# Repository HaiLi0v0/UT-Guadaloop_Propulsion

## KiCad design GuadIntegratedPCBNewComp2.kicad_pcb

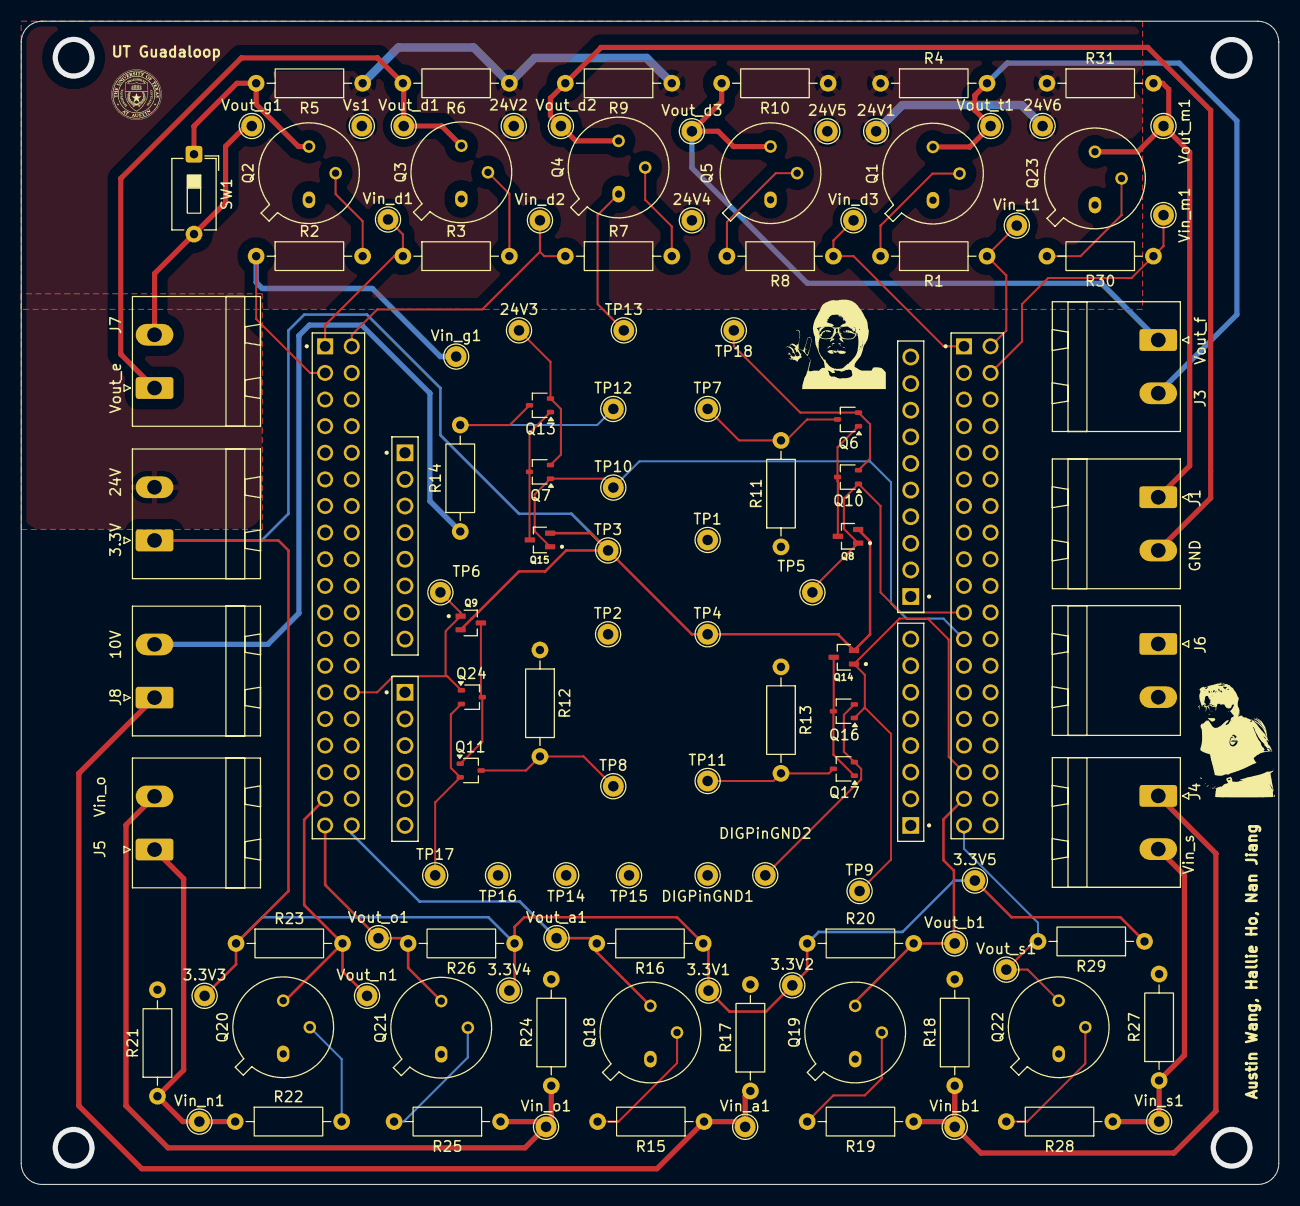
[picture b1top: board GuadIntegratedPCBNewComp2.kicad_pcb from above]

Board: 2 copper layers, 120.0 x 111.0 mm, 118 parts (0 on the bottom side), 50 nets.

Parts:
3.3V1, 3.3V2, 3.3V3, 3.3V4, 3.3V5, 24V1, 24V2, 24V4, 24V5, 24V6: Vs; TestPoint_THTPad_D2.0mm_Drill1.0mm
24V3: Vs GND; TestPoint_THTPad_D2.0mm_Drill1.0mm
DIGPinGND1, DIGPinGND2: V4 GND; TestPoint_THTPad_D2.0mm_Drill1.0mm
J1, J2, J3, J4, J5, J6, J7, J8: Screw_Terminal_01x02; PhoenixContact_MSTBA_2,5_2-G-5,08_1x02_P5.08mm_Horizontal
Q1, Q2, Q3, Q4, Q5, Q18, Q19, Q20, Q21, Q22, Q23: 2N2219; TO-39-3
Q6, Q7, Q10, Q11, Q13, Q16, Q17, Q24: BSS214NW; SOT-323_SC-70
Q8, Q9, Q14, Q15: BSS209PW_H6327; SOT65P210X100-3N
R1, R2, R3, R7, R8, R15, R19, R22, R25, R28, R30: 25k; R_Axial_DIN0207_L6.3mm_D2.5mm_P10.16mm_Horizontal
R4, R5, R6, R9, R10, R11, R12, R13, R14, R16, R20, R23, R26, R29, R31: 1200; R_Axial_DIN0207_L6.3mm_D2.5mm_P10.16mm_Horizontal
R17, R18, R21, R24, R27: 100k; R_Axial_DIN0207_L6.3mm_D2.5mm_P10.16mm_Horizontal
SW1: SW_SPST; SW_DIP_SPSTx01_Slide_6.7x4.1mm_W7.62mm_P2.54mm_LowProfile
TP1, TP2: V2 = 10 V; TestPoint_THTPad_D2.0mm_Drill1.0mm
TP3, TP4: V1 = 3.3; TestPoint_THTPad_D2.0mm_Drill1.0mm
TP5, TP6: V4 = 3.3 Pulse; TestPoint_THTPad_D2.0mm_Drill1.0mm
TP7, TP8, TP11, TP12: Vo; TestPoint_THTPad_D2.0mm_Drill1.0mm
TP9, TP10: V3 = 3.3 PULSE; TestPoint_THTPad_D2.0mm_Drill1.0mm
TP13, TP16: V1 GND; TestPoint_THTPad_D2.0mm_Drill1.0mm
TP14, TP17: V3 GND; TestPoint_THTPad_D2.0mm_Drill1.0mm
TP15, TP18: V2 GND; TestPoint_THTPad_D2.0mm_Drill1.0mm
U1: NUCLEO-F446RE; MODULE_NUCLEO-F446RE
Vin_a1: 24V; TestPoint_THTPad_D2.0mm_Drill1.0mm
Vin_b1: 5V; TestPoint_THTPad_D2.0mm_Drill1.0mm
Vin_d1, Vin_d2, Vin_d3: 5V; TestPoint_THTPad_D2.0mm_Drill1.0mm
Vin_g1: Vs; TestPoint_THTPad_D2.0mm_Drill1.0mm
Vin_m1: 5V; TestPoint_THTPad_D2.0mm_Drill1.0mm
Vin_n1: 5V; TestPoint_THTPad_D2.0mm_Drill1.0mm
Vin_o1: 5V; TestPoint_THTPad_D2.0mm_Drill1.0mm
Vin_s1: 5V; TestPoint_THTPad_D2.0mm_Drill1.0mm
Vin_t1: Vs; TestPoint_THTPad_D2.0mm_Drill1.0mm
Vout_a1: Vs; TestPoint_THTPad_D2.0mm_Drill1.0mm
Vout_b1: Vs; TestPoint_THTPad_D2.0mm_Drill1.0mm
Vout_d1, Vout_d2, Vout_d3: Vs; TestPoint_THTPad_D2.0mm_Drill1.0mm
Vout_g1: Vs; TestPoint_THTPad_D2.0mm_Drill1.0mm
Vout_m1: Vs; TestPoint_THTPad_D2.0mm_Drill1.0mm
Vout_n1: Vs; TestPoint_THTPad_D2.0mm_Drill1.0mm
Vout_o1: Vs; TestPoint_THTPad_D2.0mm_Drill1.0mm
Vout_s1: Vs; TestPoint_THTPad_D2.0mm_Drill1.0mm
Vout_t1: Vs; TestPoint_THTPad_D2.0mm_Drill1.0mm
Vs1: Vs; TestPoint_THTPad_D2.0mm_Drill1.0mm

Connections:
3.3V: 3.3V1.1, 3.3V2.1, 3.3V3.1, 3.3V4.1, 3.3V5.1, J2.1, Q8.2 (S), Q9.2 (S), Q14.2 (S), Q15.2 (S), R16.1, R20.1, R23.1, R26.1, R29.1, TP3.1, TP4.1
3v3Pulse1: Q9.1 (G), Q24.1 (G), TP6.1, U1.CN7_28 (PA0)
3v3Pulse2: Q7.1 (G), Q15.1 (G), TP10.1, U1.CN10_23 (PA8)
3v3Pulse3: Q8.1 (G), Q10.1 (G), TP5.1, U1.CN10_21 (PA9)
3v3Pulse4: Q14.1 (G), Q16.1 (G), TP9.1, U1.CN10_33 (PA10)
10v: J8.2, R11.1, R12.1, R13.1, R14.1, TP1.1, TP2.1
24v: 24V1.1, 24V2.1, 24V4.1, 24V5.1, 24V6.1, J2.2, R4.1, R5.1, R6.1, R9.1, R10.1, R31.1, Vs1.1
GND: 24V3.1, DIGPinGND1.1, DIGPinGND2.1, J6.1, J6.2, Q1.1 (E), Q2.1 (E), Q3.1 (E), Q4.1 (E), Q5.1 (E), Q6.2 (S), Q7.2 (S), Q10.2 (S), Q11.2 (S), Q13.2 (S), Q16.2 (S), Q17.2 (S), Q18.1 (E), Q19.1 (E), Q20.1 (E), Q21.1 (E), Q22.1 (E), Q23.1 (E), Q24.2 (S), R17.2, R18.2, R21.2, R24.2, R27.2, TP13.1, TP14.1, TP15.1, TP16.1, TP17.1, TP18.1, U1.CN6_6 (CN6_GND), U1.CN6_7 (CN6_GND__1)
unnamed: Q1.2 (B), R1.2
unnamed: Q2.2 (B), R2.2
unnamed: Q2.3 (C), R5.2, SW1.1 (A)
unnamed: Q3.2 (B), R3.2
unnamed: Q4.2 (B), R7.2
unnamed: Q5.2 (B), R8.2
unnamed: Q6.3 (D), R11.2, TP7.1
unnamed: Q6.1 (G), Q8.3 (D), Q10.3 (D)
unnamed: Q11.3 (D), R12.2, TP8.1
unnamed: Q9.3 (D), Q11.1 (G), Q24.3 (D)
unnamed: Q13.3 (D), R14.2, TP12.1
unnamed: Q7.3 (D), Q13.1 (G), Q15.3 (D)
unnamed: Q14.3 (D), Q16.3 (D), Q17.1 (G)
unnamed: Q17.3 (D), R13.2, TP11.1
unnamed: Q18.2 (B), R15.2
unnamed: Q19.2 (B), R19.2
unnamed: Q20.2 (B), R22.2
unnamed: Q21.2 (B), R25.2
unnamed: Q22.2 (B), R28.2
unnamed: Q23.2 (B), R30.2
Vin_a: J8.1, R15.1, R17.1, Vin_a1.1
Vin_b: J4.1, R18.1, R19.1, Vin_b1.1
Vin_e: R3.1, U1.CN7_1 (PC10), Vin_d1.1
Vin_f: R8.1, U1.CN10_1 (PC9), Vin_d3.1
Vin_g1: R2.1, U1.CN7_3 (PC12), Vin_g1.1
Vin_l: R7.1, U1.CN7_2 (PC11), Vin_d2.1
Vin_m: R30.1, U1.CN10_4 (PC6), Vin_m1.1
Vin_n: J5.1, R21.1, R22.1, Vin_n1.1
Vin_o: J5.2, R24.1, R25.1, Vin_o1.1
Vin_s: J4.2, R27.1, R28.1, Vin_s1.1
Vin_t1: R1.1, U1.CN10_2 (PC8), Vin_t1.1
Vout_a: Q18.3 (C), R16.2, U1.CN7_38 (PC0/PB8), Vout_a1.1
Vout_b: Q19.3 (C), R20.2, U1.CN10_35 (PA2), Vout_b1.1
Vout_e: J7.1, Q3.3 (C), R6.2, Vout_d1.1
Vout_f: J3.1, Q5.3 (C), R10.2, Vout_d3.1
Vout_g1: J7.2, SW1.2 (B), Vout_g1.1
Vout_l: J1.2, Q4.3 (C), R9.2, Vout_d2.1
Vout_m: J1.1, Q23.3 (C), R31.2, Vout_m1.1
Vout_n: Q20.3 (C), R23.2, U1.CN7_35 (PC2), Vout_n1.1
Vout_o: Q21.3 (C), R26.2, U1.CN7_37 (PC3), Vout_o1.1
Vout_s: Q22.3 (C), R29.2, U1.CN10_37 (PA3), Vout_s1.1
Vout_t1: J3.2, Q1.3 (C), R4.2, Vout_t1.1
